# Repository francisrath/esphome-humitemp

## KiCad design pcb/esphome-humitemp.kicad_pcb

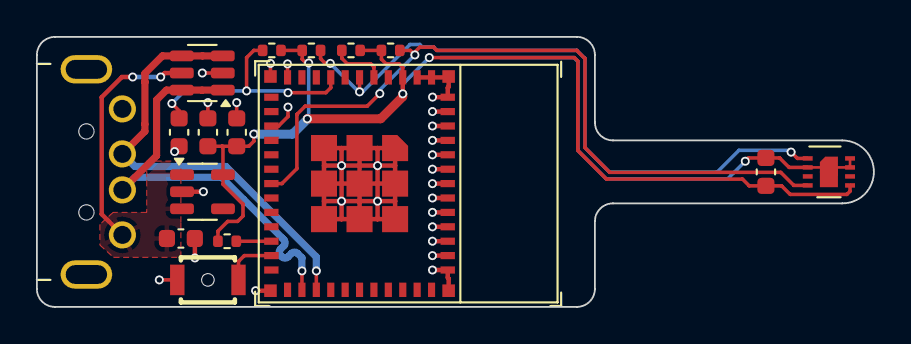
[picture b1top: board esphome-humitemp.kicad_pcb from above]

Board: 2 copper layers, 46.5 x 15.0 mm, 16 parts (0 on the bottom side), 11 nets.

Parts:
C1: 1u; C_0603_1608Metric
C2, C4: 10uF; C_0603_1608Metric
C3, C5: 0.1u; C_0603_1608Metric
J1: USB_IN; SHOU_HAN_AM90
R1, R2, R3, R4, R5: 10k; R_0402_1005Metric
SW1: RESET; SW-SMD_L3.0-W2.5-P3.40-LS4.0-EH
U1: USBLC6-4SC6; SOT-23-6
U2: TLV75533PDBV; SOT-23-5
U3: ESP32-C3-MINI-1
U4: SHT3x; Sensirion_DFN-8-1EP_2.5x2.5mm_P0.5mm_EP1.1x1.7mm

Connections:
+3V3: C3.2, C4.1, C5.2, R1.1, R2.1, R3.1, R4.1, R5.1, U2.5 (OUT), U3.3 (3V3), U4.5 (VDD)
/EN: C1.2, R3.2, U3.8 (EN/CHIP_PU)
D+: J1.3 (D+), U1.3 (I/O2), U1.4 (I/O3), U3.27 (GPIO19/USB_D+)
D-: J1.2 (D-), U1.1 (I/O1), U1.6 (I/O4), U3.26 (GPIO18/USB_D-)
GND: C1.1, C2.2, C3.1, C4.2, C5.1, J1.4 (GND), SW1.2 (B), U1.2 (GND), U2.2 (GND), U3.1 (GND), U3.2 (GND), U3.11 (GND), U3.14 (GND), U3.36 (GND), U3.37 (GND), U3.38 (GND), U3.39 (GND), U3.40 (GND), U3.41 (GND), U3.42 (GND), U3.43 (GND), U3.44 (GND), U3.45 (GND), U3.46 (GND), U3.47 (GND), U3.48 (GND), U3.49 (GND), U3.50 (GND), U3.51 (GND), U3.52 (GND), U3.53 (GND), U4.2 (ADDR), U4.7 (R), U4.8 (VSS), U4.9 (VSS)
unnamed: SW1.1 (A), U3.23 (GPIO9)
unnamed: R1.2, U3.5 (GPIO2/ADC1_CH2)
unnamed: R2.2, U3.22 (GPIO8)
SCL: R4.2, U3.18 (GPIO4/ADC1_CH4), U4.4 (SCL)
SDA: R5.2, U3.6 (GPIO3/ADC1_CH3), U4.1 (SDA)
VBUS: C2.1, J1.1 (VBUS), U1.5 (VBUS), U2.1 (IN), U2.3 (EN)

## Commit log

2024-08-29 Ready for final checking
2025-02-23 Misc
2025-03-04 KiCad 9
